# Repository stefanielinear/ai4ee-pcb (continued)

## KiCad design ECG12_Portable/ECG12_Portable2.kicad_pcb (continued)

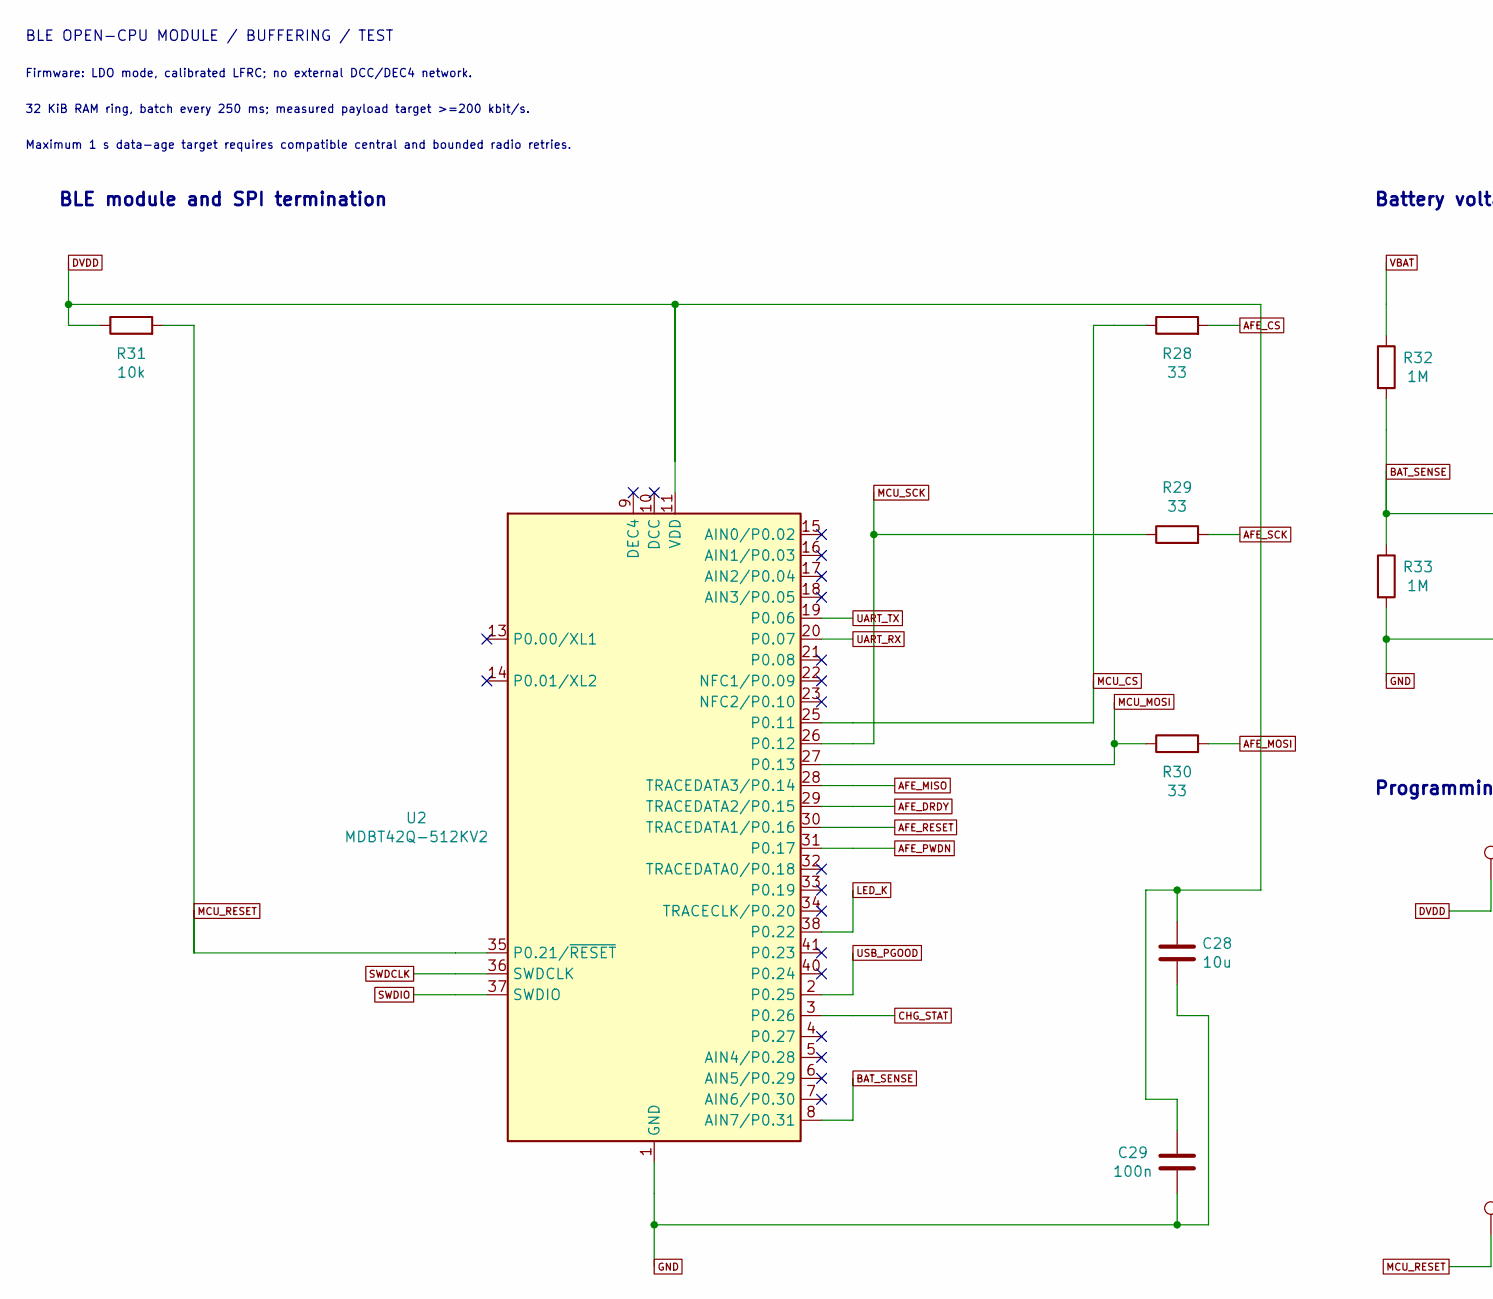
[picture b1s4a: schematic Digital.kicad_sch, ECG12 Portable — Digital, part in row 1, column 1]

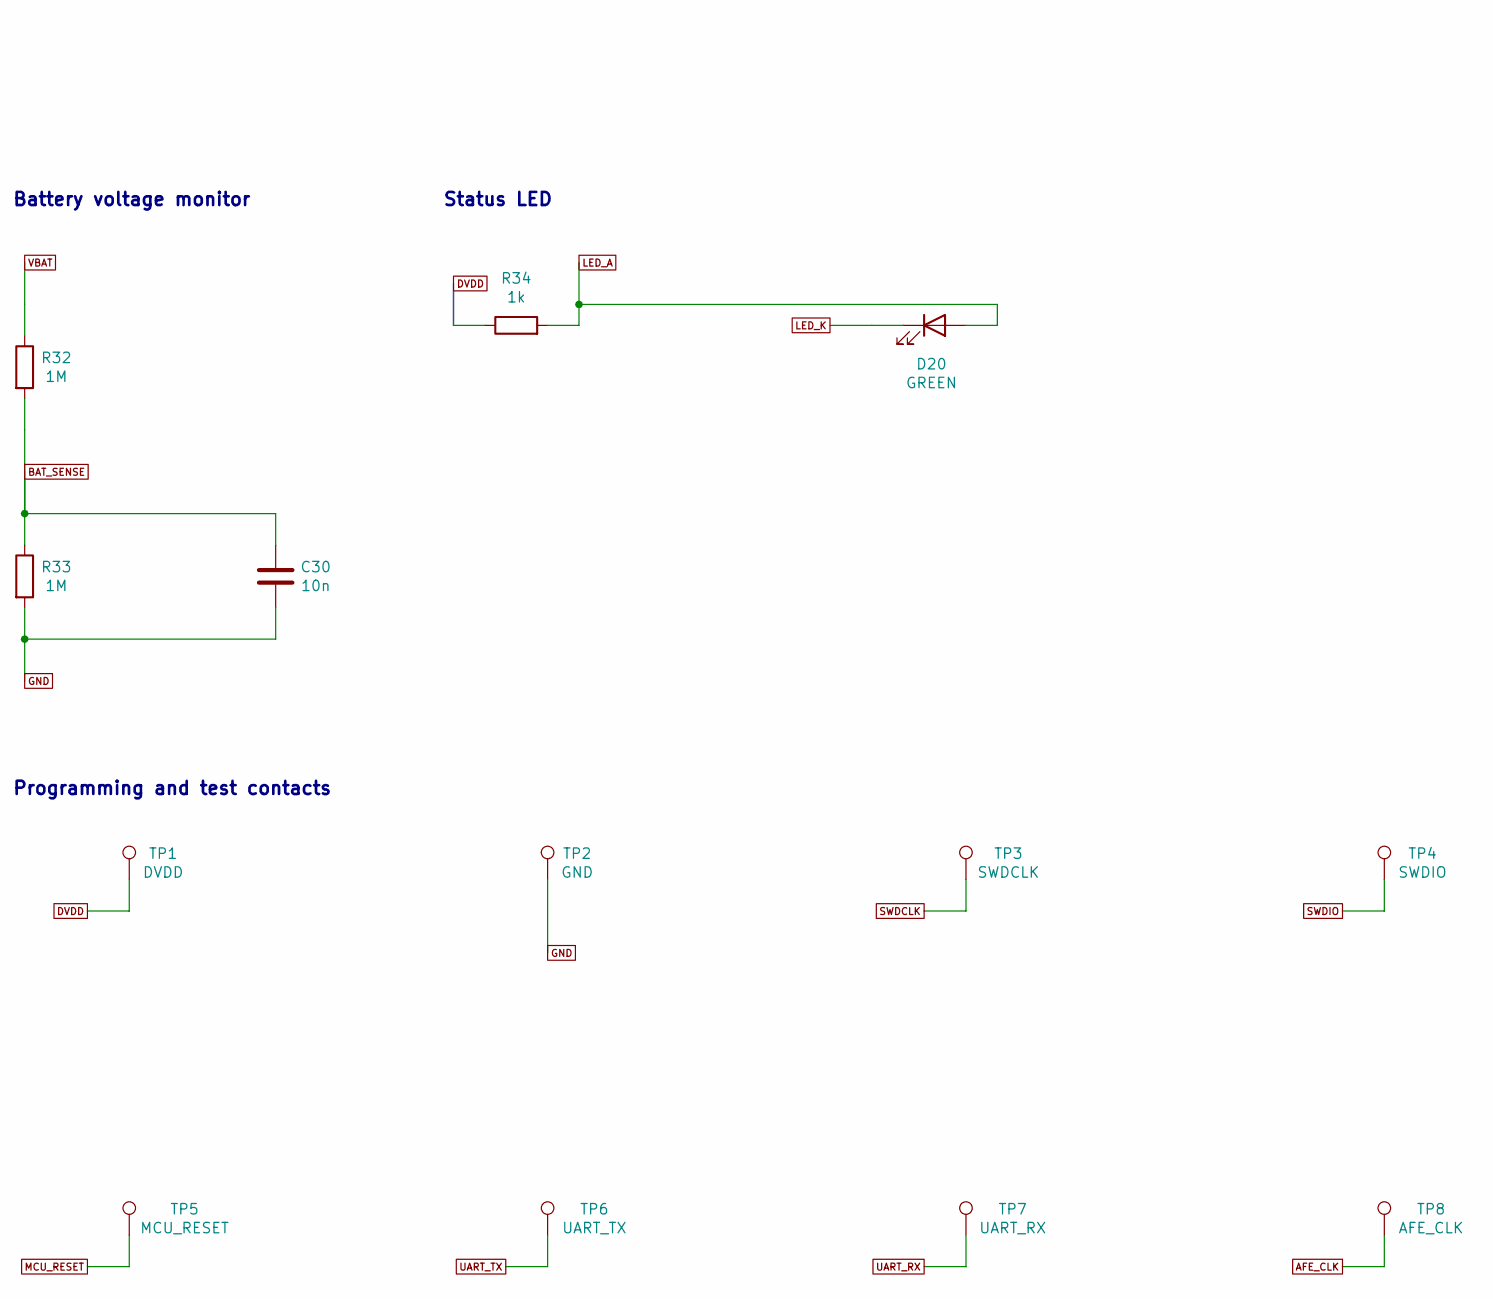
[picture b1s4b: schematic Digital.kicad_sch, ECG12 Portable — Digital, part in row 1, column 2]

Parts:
C28: 10u; Capacitor_SMD_C_0603_1608Metric; MPN GRM188R60J106ME47D
C29: 100n; Capacitor_SMD_C_0402_1005Metric; MPN GRM155R71C104KA88D
C30: 10n; Capacitor_SMD_C_0402_1005Metric; MPN GRM155R71C103KA01D
D20: GREEN; LED_SMD_LED_0603_1608Metric; MPN LTST-C190KGKT
R28, R29, R30: 33; Resistor_SMD_R_0402_1005Metric; MPN RC0402FR-0733RL
R31: 10k; Resistor_SMD_R_0402_1005Metric; MPN RC0402FR-0710KL
R32, R33: 1M; Resistor_SMD_R_0402_1005Metric; MPN RC0402FR-071ML
R34: 1k; Resistor_SMD_R_0402_1005Metric; MPN RC0402FR-071KL
TP1: DVDD; TestPoint_TestPoint_Pad_D1.0mm; MPN TEST_PAD_1MM
TP2: GND; TestPoint_TestPoint_Pad_D1.0mm; MPN TEST_PAD_1MM
TP3: SWDCLK; TestPoint_TestPoint_Pad_D1.0mm; MPN TEST_PAD_1MM
TP4: SWDIO; TestPoint_TestPoint_Pad_D1.0mm; MPN TEST_PAD_1MM
TP5: MCU_RESET; TestPoint_TestPoint_Pad_D1.0mm; MPN TEST_PAD_1MM
TP6: UART_TX; TestPoint_TestPoint_Pad_D1.0mm; MPN TEST_PAD_1MM
TP7: UART_RX; TestPoint_TestPoint_Pad_D1.0mm; MPN TEST_PAD_1MM
TP8: AFE_CLK; TestPoint_TestPoint_Pad_D1.0mm; MPN TEST_PAD_1MM
U2: MDBT42Q-512KV2; RF_Module_Raytac_MDBT42Q; MPN MDBT42Q-512KV2

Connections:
AFE_CLK: TP8.1; also elsewhere on the board
AFE_CS: R28.2; also elsewhere on the board
AFE_DRDY: U2.29 (TRACEDATA2/P0.15); also elsewhere on the board
AFE_MISO: U2.28 (TRACEDATA3/P0.14); also elsewhere on the board
AFE_MOSI: R30.2; also elsewhere on the board
AFE_PWDN: U2.31 (P0.17); also elsewhere on the board
AFE_RESET: U2.30 (TRACEDATA1/P0.16); also elsewhere on the board
AFE_SCK: R29.2; also elsewhere on the board
BAT_SENSE: C30.1, R32.2, R33.1, U2.8 (AIN7/P0.31)
CHG_STAT: U2.3 (P0.26); also elsewhere on the board
DVDD: C28.1, C29.1, R31.1, R34.1, TP1.1, U2.11 (VDD); also elsewhere on the board
GND: C28.2, C29.2, C30.2, R33.2, TP2.1, U2.1 (GND), U2.12 (GND), U2.24 (GND), U2.39 (GND); also elsewhere on the board
LED_A: D20.2 (A), R34.2
LED_K: D20.1 (K), U2.38 (P0.22)
MCU_CS: R28.1, U2.25 (P0.11)
MCU_MOSI: R30.1, U2.27 (P0.13)
MCU_RESET: R31.2, TP5.1, U2.35 (P0.21/~RESET)
MCU_SCK: R29.1, U2.26 (P0.12)
SWDCLK: TP3.1, U2.36 (SWDCLK)
SWDIO: TP4.1, U2.37 (SWDIO)
UART_RX: TP7.1, U2.20 (P0.07)
UART_TX: TP6.1, U2.19 (P0.06)
USB_PGOOD: U2.2 (P0.25); also elsewhere on the board
VBAT: R32.1; also elsewhere on the board

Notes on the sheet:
BLE OPEN-CPU MODULE / BUFFERING / TEST
Firmware: LDO mode, calibrated LFRC; no external DCC/DEC4 network.
32 KiB RAM ring, batch every 250 ms; measured payload target >=200 kbit/s.
Maximum 1 s data-age target requires compatible central and bounded radio retries.
BLE module and SPI termination
Battery voltage monitor
Status LED
Programming and test contacts

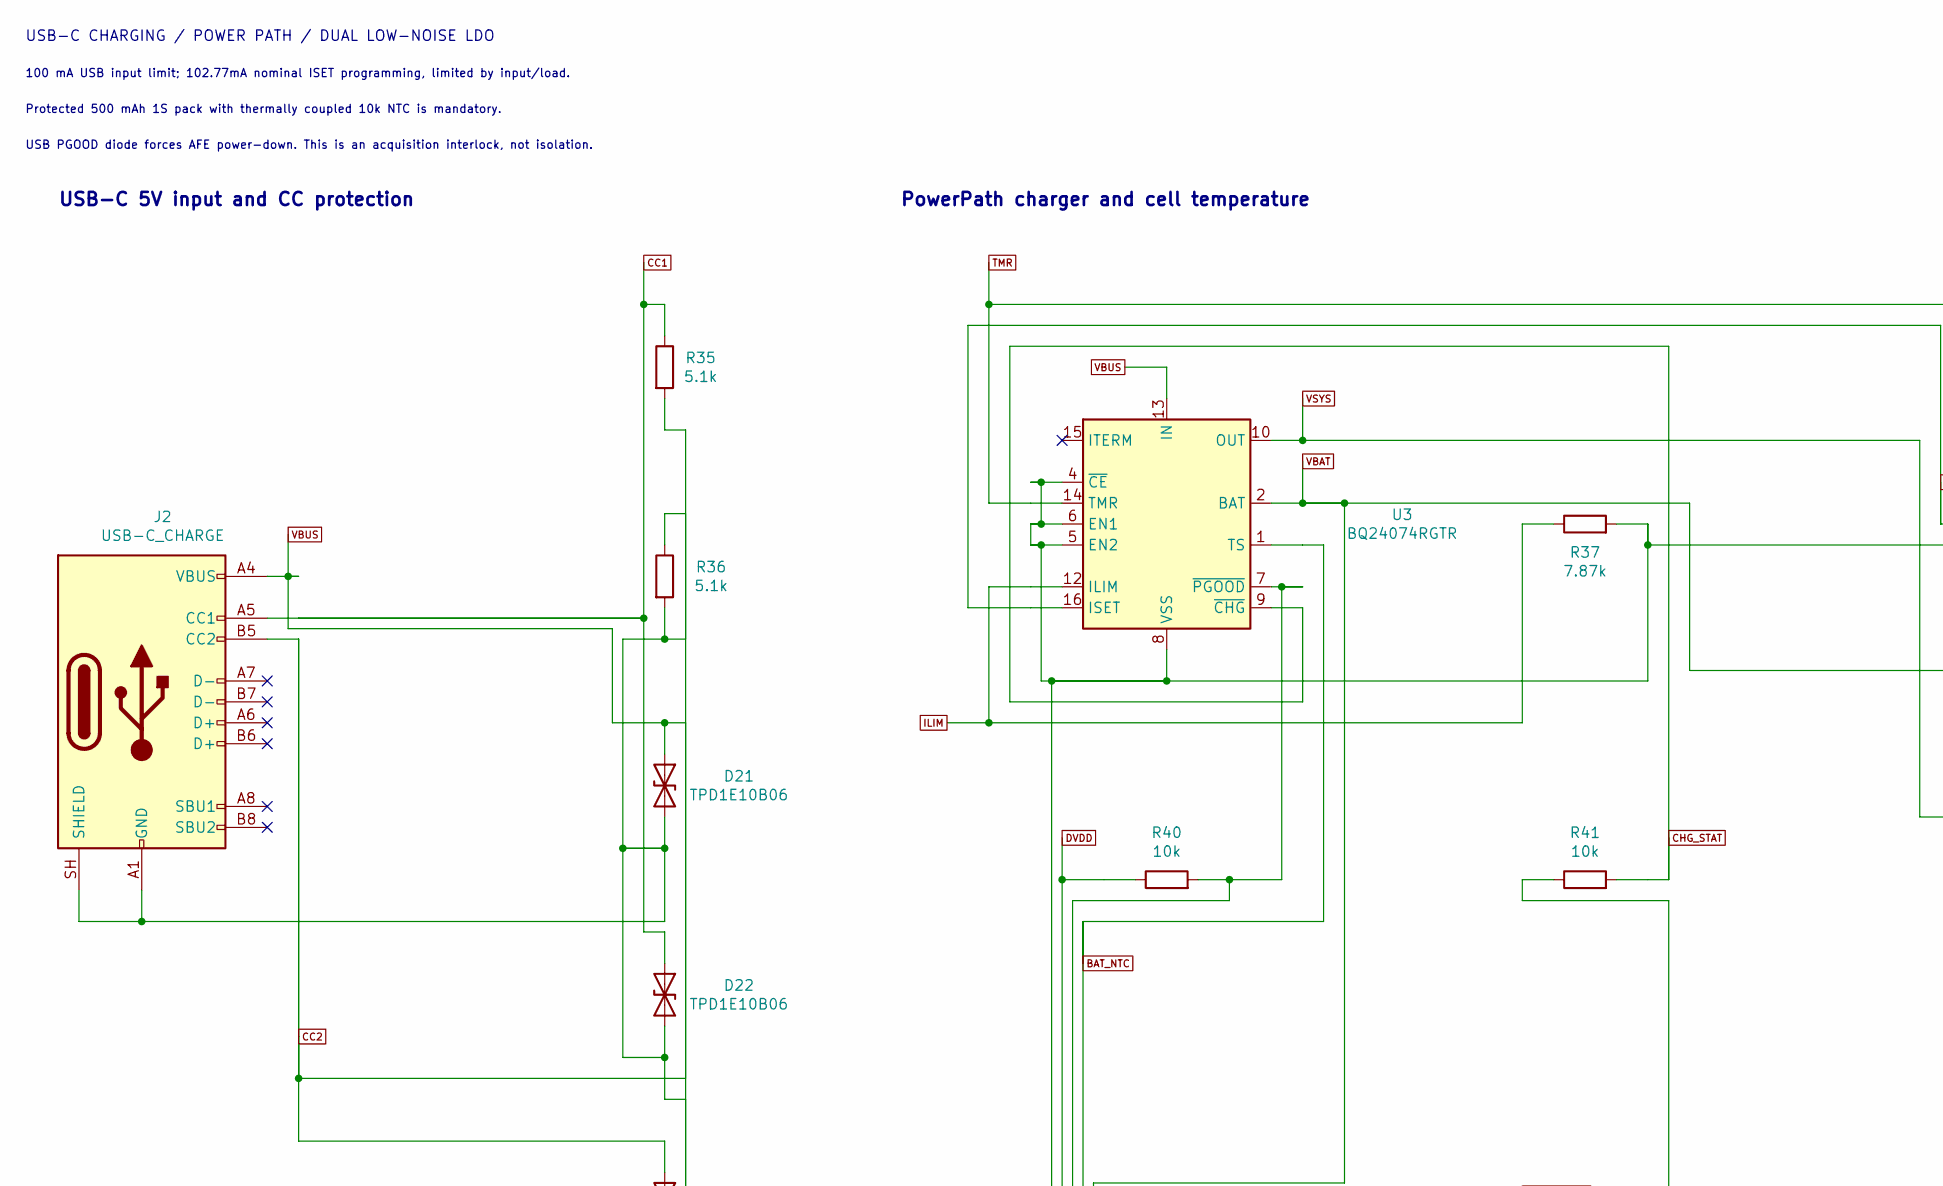
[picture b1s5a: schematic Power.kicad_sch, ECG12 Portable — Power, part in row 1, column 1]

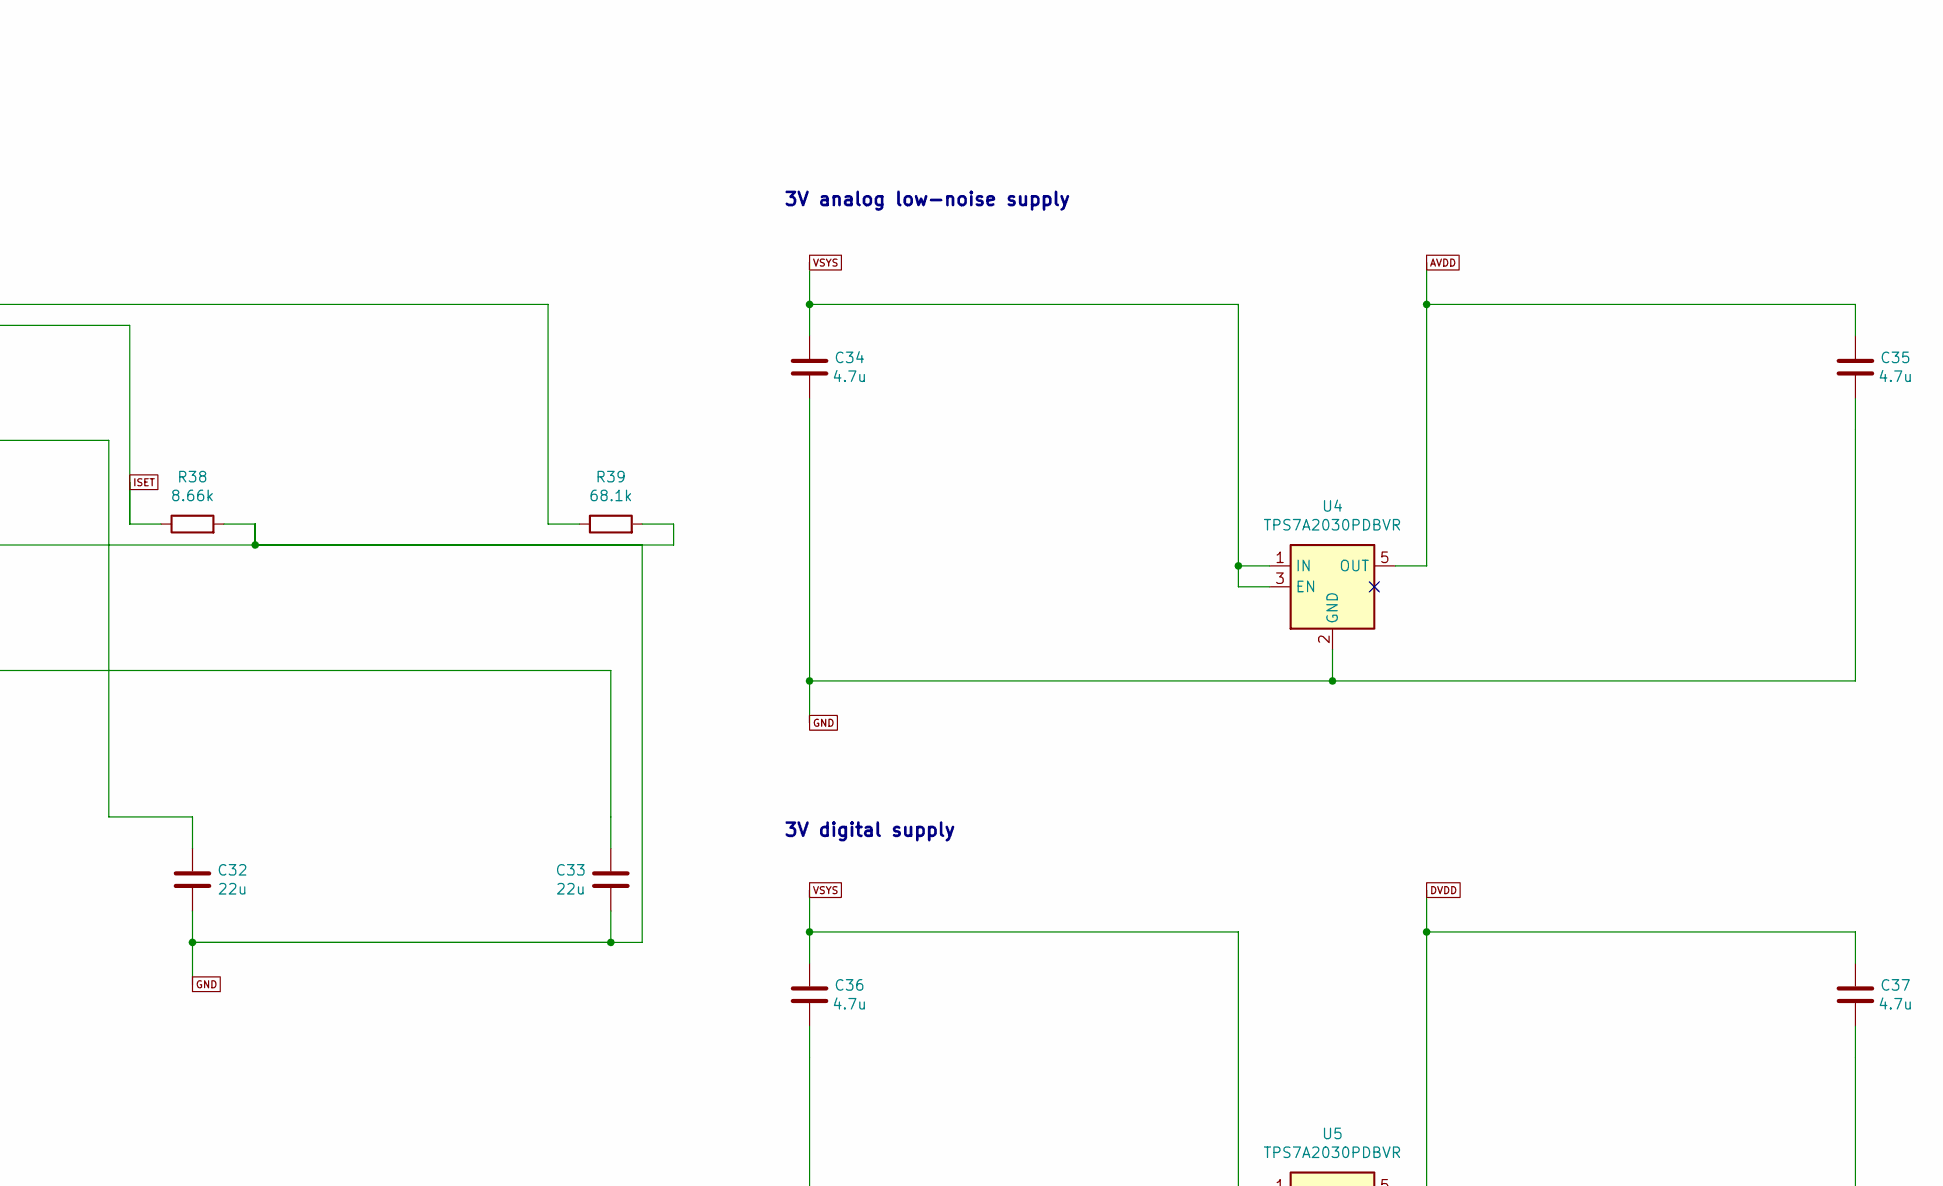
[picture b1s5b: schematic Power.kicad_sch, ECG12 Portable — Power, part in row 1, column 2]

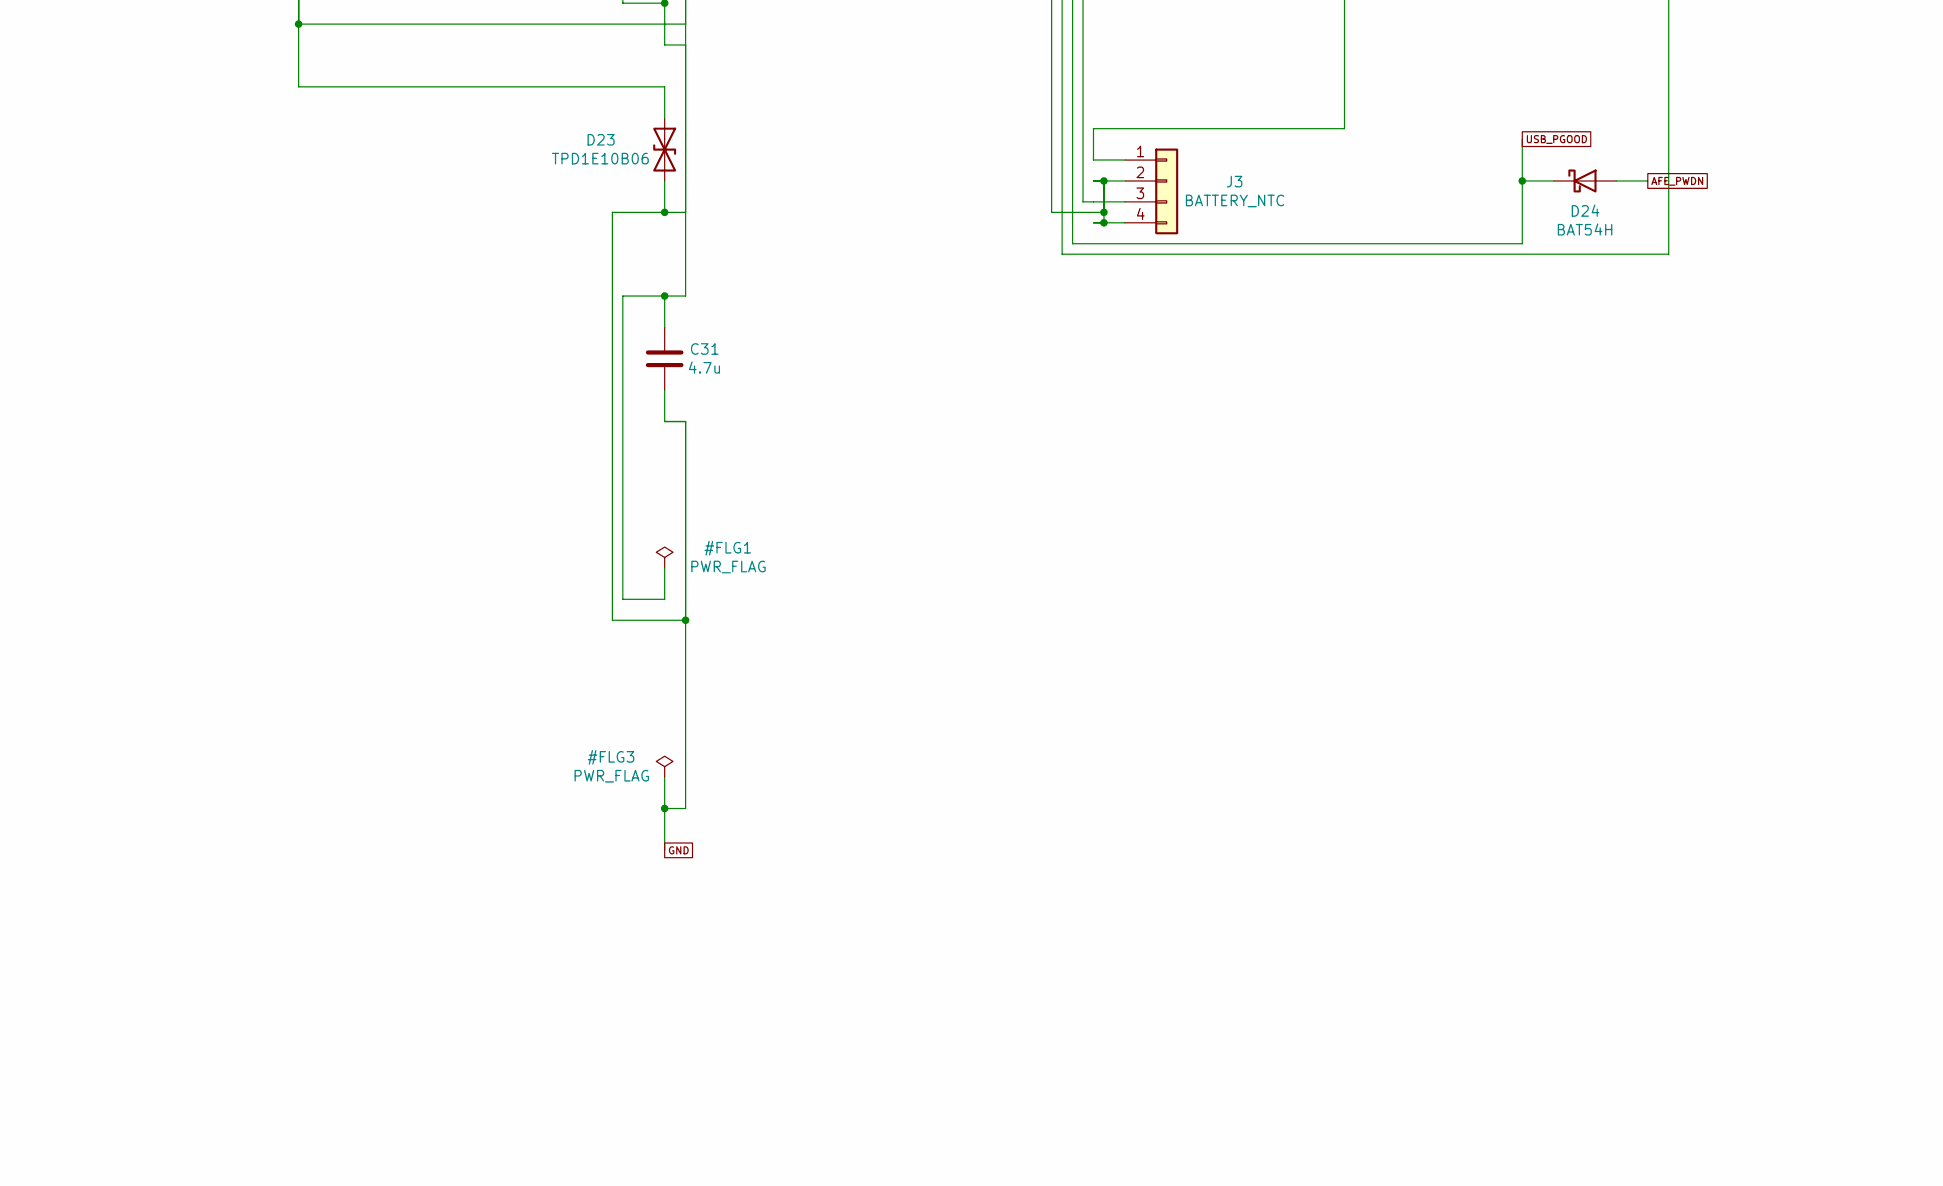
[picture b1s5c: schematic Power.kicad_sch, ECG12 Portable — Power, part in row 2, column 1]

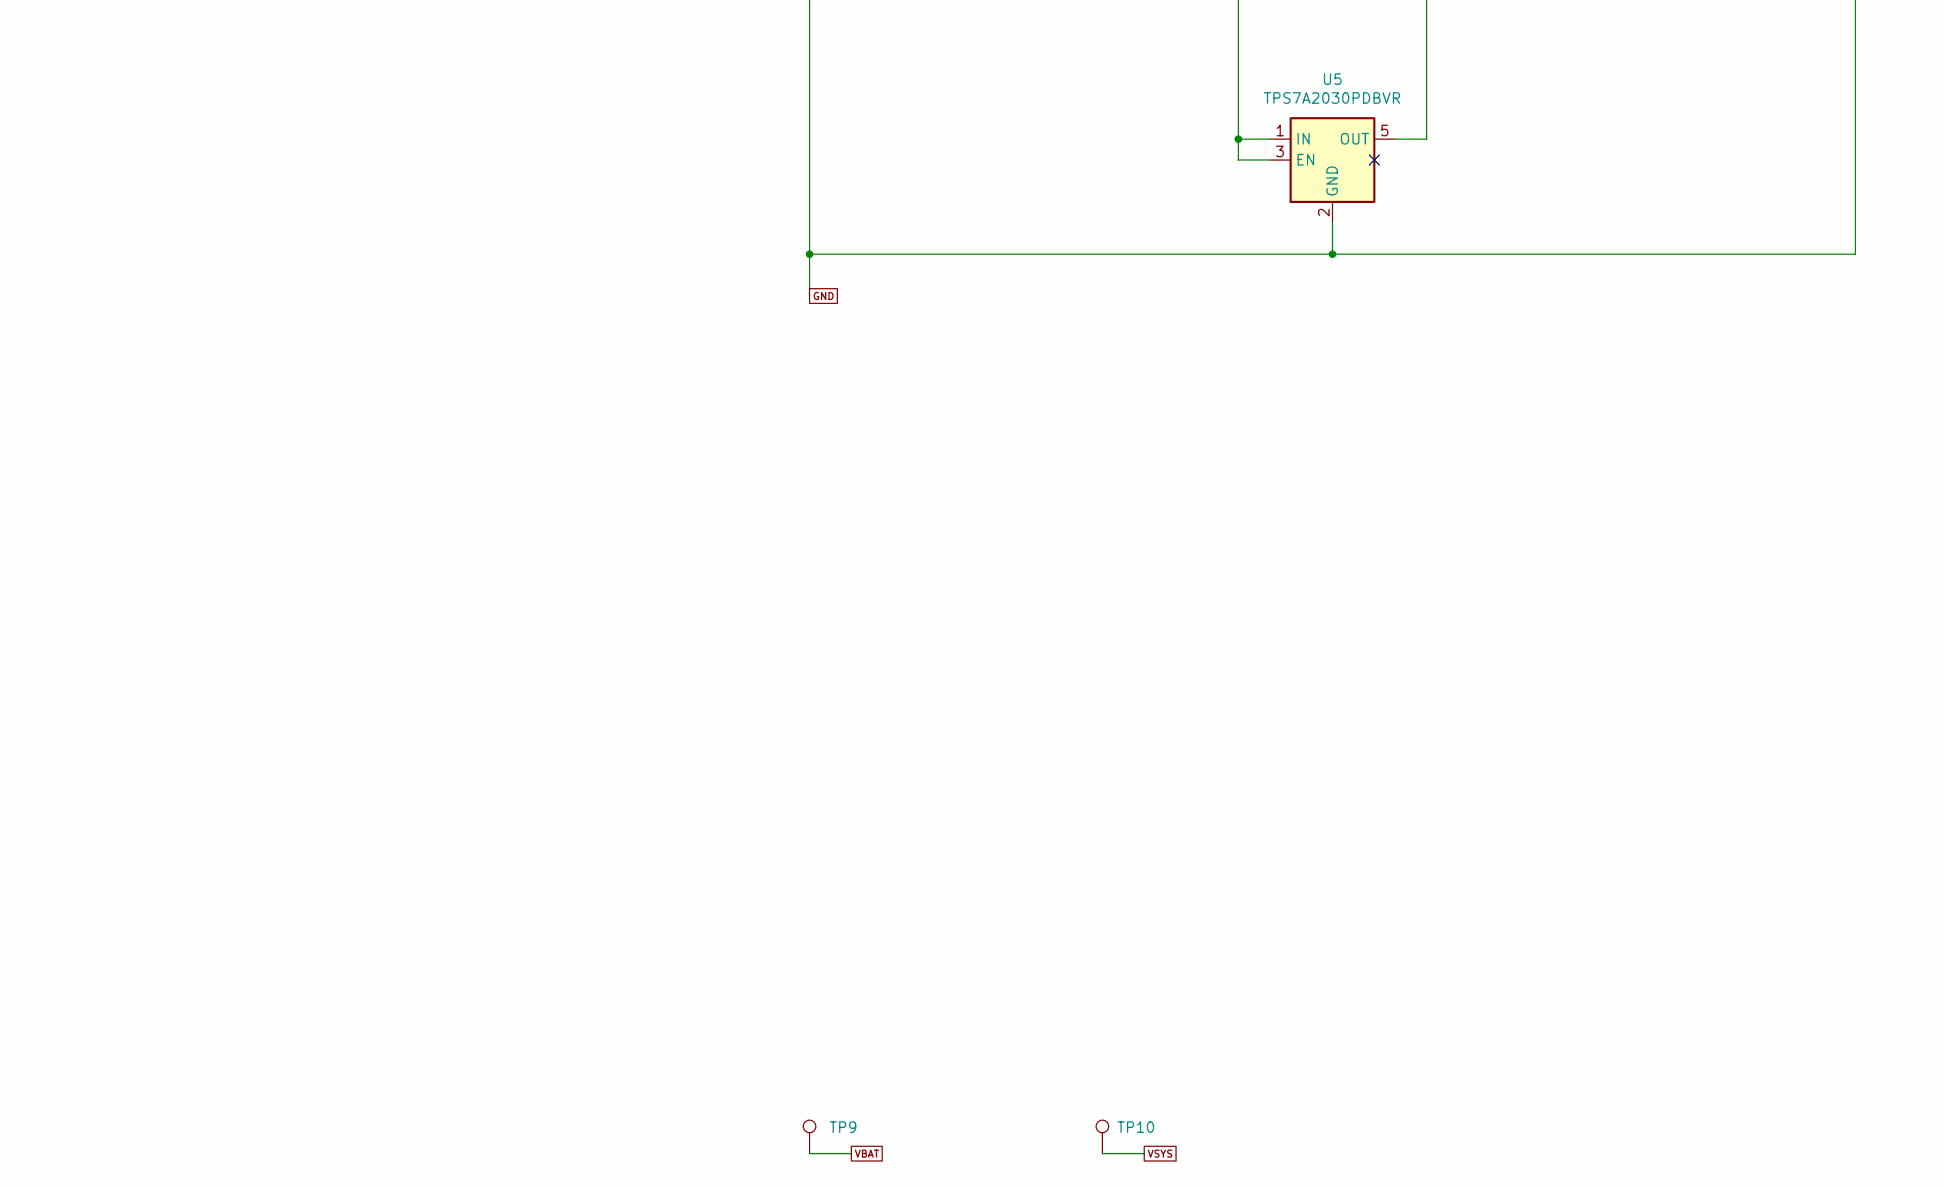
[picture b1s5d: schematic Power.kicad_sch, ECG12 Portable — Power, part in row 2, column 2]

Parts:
C31, C34, C35, C36, C37: 4.7u; Capacitor_SMD_C_0603_1608Metric; Voltage 16V; Tolerance 10%; MPN C1608X5R1C475K080AC
C32, C33: 22u; Capacitor_SMD_C_0805_2012Metric; Voltage 25V; Tolerance 20%; MPN C2012X5R1E226M125AC
D21, D22, D23: TPD1E10B06; Diode_SMD_D_SOD-523; MPN TPD1E10B06DYAR
D24: BAT54H; Diode_SMD_D_SOD-123F; MPN BAT54H,115
J2: USB-C_CHARGE; Connector_USB_USB_C_Receptacle_HRO_TYPE-C-31-M-12; MPN TYPE-C-31-M-12
J3: BATTERY_NTC; Connector_JST_JST_SH_BM04B-SRSS-TB_1x04-1MP_P1.00mm_Vertical; MPN BM04B-SRSS-TB(LF)(SN)
R35, R36: 5.1k; Resistor_SMD_R_0402_1005Metric; MPN RC0402FR-075K1L
R37: 7.87k; Resistor_SMD_R_0402_1005Metric; MPN RC0402FR-077K87L
R38: 8.66k; Resistor_SMD_R_0402_1005Metric; MPN RC0402FR-078K66L
R39: 68.1k; Resistor_SMD_R_0402_1005Metric; MPN RC0402FR-0768K1L
R40, R41: 10k; Resistor_SMD_R_0402_1005Metric; MPN RC0402FR-0710KL
TP9: VBAT; TestPoint_TestPoint_Pad_D1.0mm; MPN TEST_PAD_1MM
TP10: VSYS; TestPoint_TestPoint_Pad_D1.0mm; MPN TEST_PAD_1MM
U3: BQ24074RGTR; Package_DFN_QFN_VQFN-16-1EP_3x3mm_P0.5mm_EP1.6x1.6mm; MPN BQ24074RGTR
U4, U5: TPS7A2030PDBVR; Package_TO_SOT_SMD_SOT-23-5; MPN TPS7A2030PDBVR

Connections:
AFE_PWDN: D24.2 (A); also elsewhere on the board
AVDD: C35.1, U4.5 (OUT); also elsewhere on the board
BAT_NTC: J3.3, U3.1 (TS)
CC1: D22.1 (A1), J2.A5 (CC1), R35.1
CC2: D23.1 (A1), J2.B5 (CC2), R36.1
CHG_STAT: R41.2, U3.9 (~CHG); also elsewhere on the board
DVDD: C37.1, R40.1, R41.1, U5.5 (OUT); also elsewhere on the board
GND: C31.2, C32.2, C33.2, C34.2, C35.2, C36.2, C37.2, D21.2 (A2), D22.2 (A2), D23.2 (A2), J2.A1 (GND), J2.A12 (GND), J2.B1 (GND), J2.B12 (GND), J2.SH (SHIELD), J3.2, J3.4, R35.2, R36.2, R37.2, R38.2, R39.2, U3.4 (~CE), U3.5 (EN2), U3.6 (EN1), U3.8 (VSS), U3.17 (VSS), U4.2 (GND), U5.2 (GND); also elsewhere on the board
ILIM: R37.1, U3.12 (ILIM)
ISET: R38.1, U3.16 (ISET)
TMR: R39.1, U3.14 (TMR)
USB_PGOOD: D24.1 (K), R40.2, U3.7 (~PGOOD); also elsewhere on the board
VBAT: C33.1, J3.1, TP9.1, U3.2 (BAT), U3.3 (BAT); also elsewhere on the board
VBUS: C31.1, D21.1 (A1), J2.A4 (VBUS), J2.A9 (VBUS), J2.B4 (VBUS), J2.B9 (VBUS), U3.13 (IN)
VSYS: C32.1, C34.1, C36.1, TP10.1, U3.10 (OUT), U3.11 (OUT), U4.1 (IN), U4.3 (EN), U5.1 (IN), U5.3 (EN)

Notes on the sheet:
USB-C CHARGING / POWER PATH / DUAL LOW-NOISE LDO
100 mA USB input limit; 102.77mA nominal ISET programming, limited by input/load.
Protected 500 mAh 1S pack with thermally coupled 10k NTC is mandatory.
USB PGOOD diode forces AFE power-down. This is an acquisition interlock, not isolation.
USB-C 5V input and CC protection
PowerPath charger and cell temperature
3V analog low-noise supply
3V digital supply

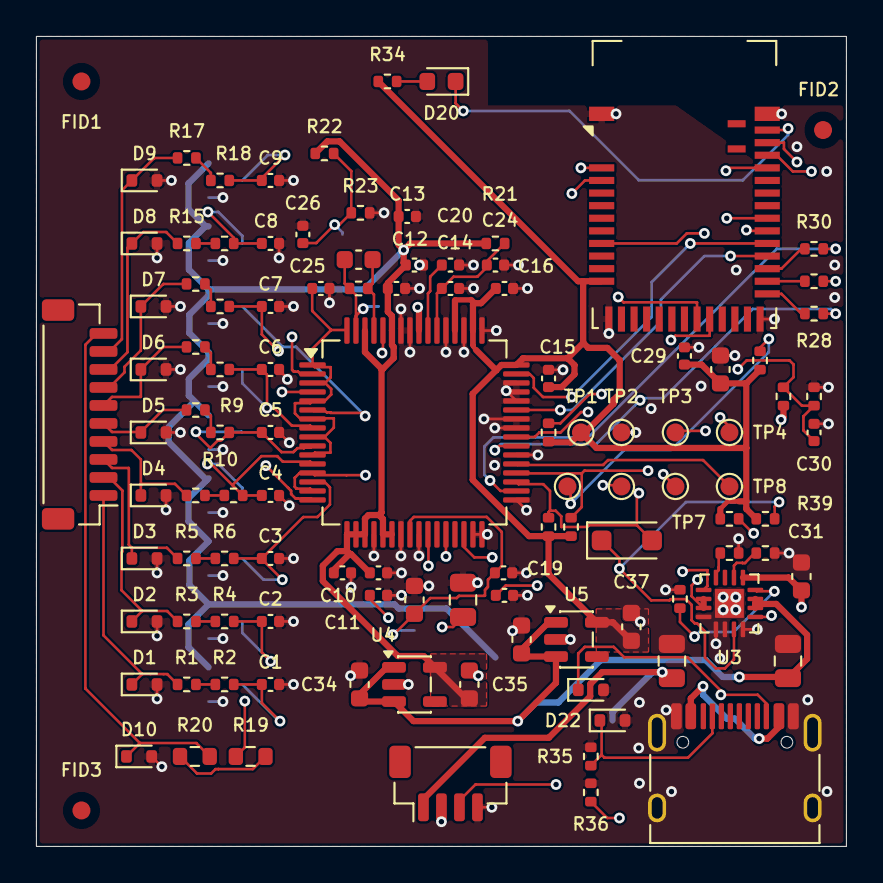
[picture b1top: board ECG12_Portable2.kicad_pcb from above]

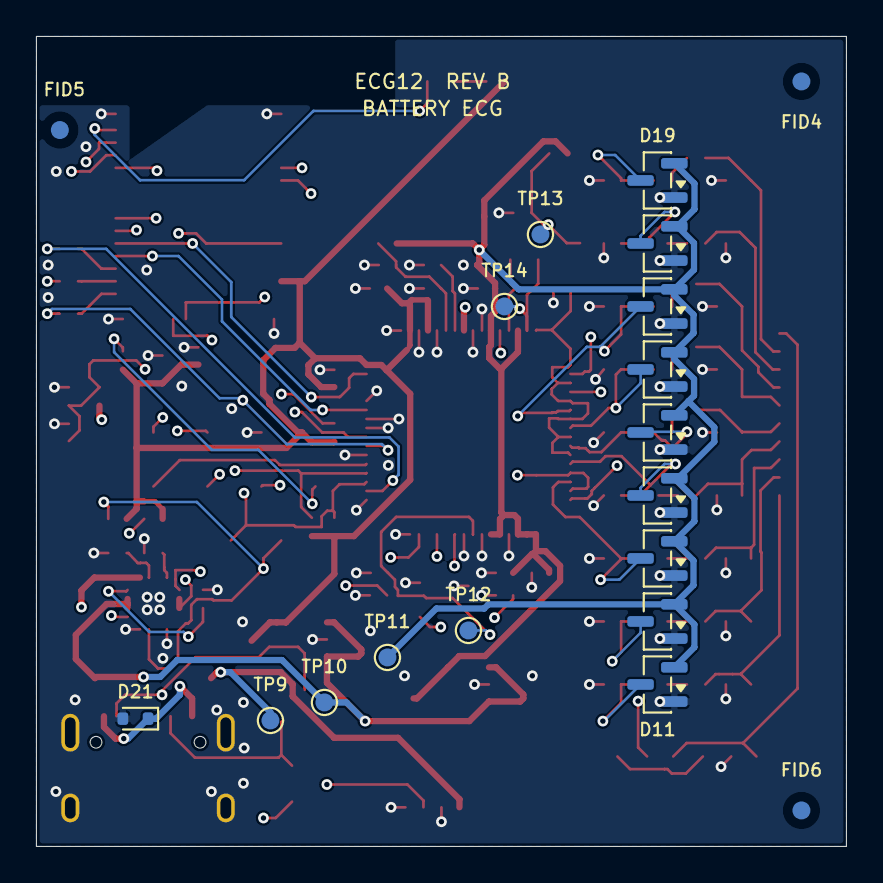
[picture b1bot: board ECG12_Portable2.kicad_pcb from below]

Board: 4 copper layers, 45.0 x 45.0 mm, 130 parts (19 on the bottom side), 72 nets.

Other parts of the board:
FID1, FID2, FID3, FID4, FID5, FID6: FIDUCIAL; Fiducial_Fiducial_1mm_Mask2mm

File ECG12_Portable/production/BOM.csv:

References,Quantity,Value,Footprint,MPN,Manufacturer,Datasheet,Notes
C1,1,200p,ECG12:Capacitor_SMD_C_0402_1005Metric,C0402C201F5GACTU,KEMET,https://search.kemet.com/component-documentation/download/sp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,"Rev B: C0G, 1%, 50V; same KEMET family. Nominal RA loading compensation retained; system CMRR requires measurement."
C2-C9,8,220p,ECG12:Capacitor_SMD_C_0402_1005Metric,C0402C221F5GACTU,KEMET,https://search.kemet.com/component-documentation/download/sp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,"Rev B: C0G, 1%, 50V; same KEMET family. Nominal RA loading compensation retained; system CMRR requires measurement."
"C10-C13,C15,C16,C22,C23,C26,C29",10,100n,ECG12:Capacitor_SMD_C_0402_1005Metric,GRM155R71C104KA88D,Murata,https://www.murata.com/en-us/products/capacitor/ceramiccapacitor,
"C14,C17,C19,C24",4,1u,ECG12:Capacitor_SMD_C_0402_1005Metric,GRM155R61A105KE15D,Murata,https://www.murata.com/en-us/products/capacitor/ceramiccapacitor,
C18,1,22u,ECG12:Capacitor_SMD_C_0805_2012Metric,GRM21BR60J226ME39L,Murata,https://www.murata.com/en-us/products/capacitor/ceramiccapacitor,
C20,1,1u,ECG12:Capacitor_SMD_C_0402_1005Metric,GRM155R61A105KE15D,Murata,https://www.murata.com/en-us/products/capacitor/ceramiccapacitor,Local AFE bypass; VCAP3 rated 10 V for boosted internal node.
"C21,C28",2,10u,ECG12:Capacitor_SMD_C_0603_1608Metric,GRM188R60J106ME47D,Murata,https://www.murata.com/en-us/products/capacitor/ceramiccapacitor,
C25,1,100p,ECG12:Capacitor_SMD_C_0402_1005Metric,GRM1555C1H101JA01D,Murata,https://www.murata.com/en-us/products/capacitor/ceramiccapacitor,
C27,1,1.5n,ECG12:Capacitor_SMD_C_0603_1608Metric,GRM1885C1H152JA01D,Murata,https://www.murata.com/en-us/products/capacitor/ceramiccapacitor,Rev B local RLD compensation parallel to R24. Validate cable/electrode loop stability.
C30,1,10n,ECG12:Capacitor_SMD_C_0402_1005Metric,GRM155R71C103KA01D,Murata,https://www.murata.com/en-us/products/capacitor/ceramiccapacitor,
"C31,C34-C37",5,4.7u,ECG12:Capacitor_SMD_C_0603_1608Metric,C1608X5R1C475K080AC,TDK,https://product.tdk.com/system/files/dam/doc/product/capacit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,Rev B: 4.7uF16V X5R0603; effective-capacitance characterization included in datasheets/revB; verify lot/DC bias margin.
"C32,C33",2,22u,ECG12:Capacitor_SMD_C_0805_2012Metric,C2012X5R1E226M125AC,TDK,https://product.tdk.cn/system/files/dam/doc/product/capacito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,Rev B: 22uF25V X5R0805; 50% bias retention x80% tolerance x85% temperature x80% aging gives 5.984uF. Typical curve only; lot acceptance >=4.7uF effective at operating bias required.
D1-D9,9,TPD1E10B06,ECG12:Diode_SMD_D_SOD-523,TPD1E10B06DYAR,Texas Instruments,https://www.ti.com/lit/ds/symlink/tpd1e10b06.pdf,Connector-side ESD. No defibrillator protection.
"D10,D21-D23",4,TPD1E10B06,ECG12:Diode_SMD_D_SOD-523,TPD1E10B06DYAR,Texas Instruments,https://www.ti.com/lit/ds/symlink/tpd1e10b06.pdf,
D11-D19,9,BAV199,ECG12:Package_TO_SOT_SMD_SOT-23,"BAV199,215",Nexperia,https://assets.nexperia.com/documents/data-sheet/BAV199.pdf,Pin 1 A1=GND; pin 2 K2=AVDD; pin 3 junction=input.
D20,1,GREEN,ECG12:LED_SMD_LED_0603_1608Metric,LTST-C190KGKT,Lite-On,https://optoelectronics.liteon.com/upload/download/DS22-2000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,
D24,1,BAT54H,ECG12:Diode_SMD_D_SOD-123F,"BAT54H,115",Nexperia,https://assets.nexperia.com/documents/data-sheet/BAT54H.pdf,USB PGOOD low inhibits acquisition. This is NOT galvanic isolation.
J1,1,ELECTRODES,ECG12:Connector_JST_JST_SH_BM10B-SRSS-TB_1x10-1MP_P1.00mm_Vertical,BM10B-SRSS-TB(LF)(SN),JST,https://www.jst-mfg.com/product/pdf/eng/eSH.pdf,1 RA; 2 LA; 3 LL; 4-9 V1-V6; 10 RL. Keyed external patient cable.
J2,1,USB-C_CHARGE,ECG12:Connector_USB_USB_C_Receptacle_HRO_TYPE-C-31-M-12,TYPE-C-31-M-12,HRO,https://datasheet.lcsc.com/datasheet/pdf/9e56b777c022540fcce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,Rev B: locating-hole center to bottom PCB edge=5.79mm per manufacturer drawing. Charge only; independent CC Rd. Verify cable/enclosure mating on prototype.
J3,1,BATTERY_NTC,ECG12:Connector_JST_JST_SH_BM04B-SRSS-TB_1x04-1MP_P1.00mm_Vertical,BM04B-SRSS-TB(LF)(SN),JST,https://www.jst-mfg.com/product/pdf/eng/eSH.pdf,"Protected 1S 500mAh cell; 10k 103AT NTC cell coupled. Pin1 +, pin2 -, pin3 NTC, pin4 NTC return."
"R1,R3,R5,R7,R9,R11,R13,R15,R17",9,100k,ECG12:Resistor_SMD_R_0402_1005Metric,RT0402BRD07100KL,Yageo,https://www.yageo.com/upload/media/product/productsearch/dat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,"0.1%, 25 ppm/K; electrode current limit stage 1"
"R2,R4,R6,R8,R10,R12,R14,R16,R18",9,100k,ECG12:Resistor_SMD_R_0402_1005Metric,RT0402BRD07100KL,Yageo,https://www.yageo.com/upload/media/product/productsearch/dat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,"0.1%, 25 ppm/K; electrode current limit stage 2"
R19,1,499k,ECG12:Resistor_SMD_R_0603_1608Metric,RC0603FR-07499KL,Yageo,https://www.yageo.com/upload/media/product/productsearch/dat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,Patient bias current limiting; two independent series resistors.
R20,1,499k,ECG12:Resistor_SMD_R_0603_1608Metric,RC0603FR-07499KL,Yageo,https://www.yageo.com/upload/media/product/productsearch/dat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,
R21,1,100,ECG12:Resistor_SMD_R_0402_1005Metric,RC0402FR-07100RL,Yageo,https://www.yageo.com/upload/media/product/productsearch/dat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,
"R22,R23",2,100k,ECG12:Resistor_SMD_R_0402_1005Metric,RC0402FR-07100KL,Yageo,https://www.yageo.com/upload/media/product/productsearch/dat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,
R24,1,1M,ECG12:Resistor_SMD_R_0402_1005Metric,RC0402FR-071ML,Yageo,https://www.yageo.com/upload/media/product/productsearch/dat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,Rev B local RLD feedback adjacent to U1 pins61/63; keep summing node short.
"R25-R27,R31,R40,R41",6,10k,ECG12:Resistor_SMD_R_0402_1005Metric,RC0402FR-0710KL,Yageo,https://www.yageo.com/upload/media/product/productsearch/dat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,
R28-R30,3,33,ECG12:Resistor_SMD_R_0402_1005Metric,RC0402FR-0733RL,Yageo,https://www.yageo.com/upload/media/product/productsearch/dat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,Source termination adjacent to MCU; 1-2 MHz SPI.
"R32,R33",2,1M,ECG12:Resistor_SMD_R_0402_1005Metric,RC0402FR-071ML,Yageo,https://www.yageo.com/upload/media/product/productsearch/dat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,
R34,1,1k,ECG12:Resistor_SMD_R_0402_1005Metric,RC0402FR-071KL,Yageo,https://www.yageo.com/upload/media/product/productsearch/dat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,
"R35,R36",2,5.1k,ECG12:Resistor_SMD_R_0402_1005Metric,RC0402FR-075K1L,Yageo,https://www.yageo.com/upload/media/product/productsearch/dat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,
R37,1,7.87k,ECG12:Resistor_SMD_R_0402_1005Metric,RC0402FR-077K87L,Yageo,https://www.yageo.com/upload/media/product/productsearch/dat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,
R38,1,8.66k,ECG12:Resistor_SMD_R_0402_1005Metric,RC0402FR-078K66L,Yageo,https://www.yageo.com/upload/media/product/productsearch/dat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,Rev B: 8.66k 1%; max 8.7466k below 8.9k. Programmed ICHG typ 102.77mA; USB100 input still limits total current.
R39,1,68.1k,ECG12:Resistor_SMD_R_0402_1005Metric,RC0402FR-0768K1L,Yageo,https://www.yageo.com/upload/media/product/productsearch/dat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,Rev B: 68.1k; nominal fast-charge safety timer 9.08h (KTMR=48s/kohm); static tolerance range 6.742-11.464h.
U1,1,ADS1298IPAG,ECG12:Package_QFP_TQFP-64_10x10mm_P0.5mm,ADS1298IPAG,Texas Instruments,http://www.ti.com/lit/ds/symlink/ads1298.pdf,"Gain 6, LP 500 SPS; internal oscillator. START commands via SPI. WCT1=0x09; WCT2=0xC2. Unused GPIO remain inputs."
U2,1,MDBT42Q-512KV2,ECG12:RF_Module_Raytac_MDBT42Q,MDBT42Q-512KV2,Raytac,https://www.raytac.com/upload/download_files/38a8a4a0aff945d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,LDO mode only; internal LFRC calibrated by BLE stack; DEC4 capacitor internal. Leave DCC/DEC4 externally open. Antenna keepout all copper layers.
U3,1,BQ24074RGTR,ECG12:Package_DFN_QFN_VQFN-16-1EP_3x3mm_P0.5mm_EP1.6x1.6mm,BQ24074RGTR,Texas Instruments,http://www.ti.com/lit/ds/symlink/bq24074.pdf,"USB100 mode: 100mA total input limit. ISET typ 102.77mA; ITERM NC in USB100 =3.3% typ, about3.39mA. External10k NTC required. Four EP thermal vias."
"U4,U5",2,TPS7A2030PDBVR,ECG12:Package_TO_SOT_SMD_SOT-23-5,TPS7A2030PDBVR,Texas Instruments,https://www.ti.com/lit/ds/symlink/tps7a20.pdf,3.0 V fixed low-noise LDO. Pin4 NC.
